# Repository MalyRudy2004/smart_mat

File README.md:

# smart_mat
Optical fiber floor mat

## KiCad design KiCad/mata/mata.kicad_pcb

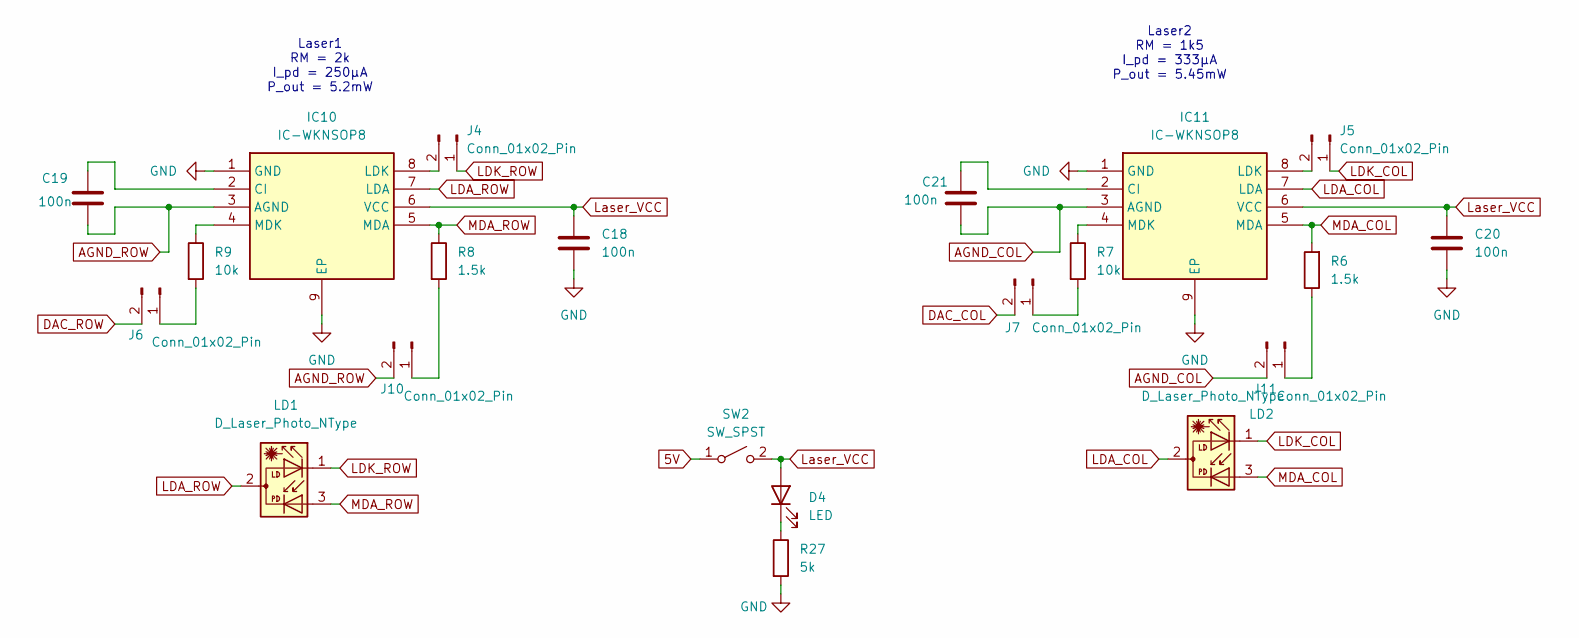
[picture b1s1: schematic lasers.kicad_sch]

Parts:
C18, C19, C20, C21: 100n; C_0805_2012Metric
D4: LED; LED_0805_2012Metric
IC10, IC11: IC-WKNSOP8; SOIC-8-1EP_3.9x4.9mm_P1.27mm_EP2.29x3mm; Manufacturer_Part_Number IC-WKNSOP8
J4, J5, J6, J7, J10, J11: Conn_01x02_Pin; PinHeader_1x02_P2.54mm_Vertical
LD1, LD2: D_Laser_Photo_NType; LaserDiode_TO56-3
R6, R8: 1.5k; R_0805_2012Metric
R7, R9: 10k; R_0805_2012Metric
R27: 5k; R_0805_2012Metric
SW2: SW_SPST; PinHeader_1x02_P2.54mm_Vertical

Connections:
5V: SW2.1 (A); also elsewhere on the board
AGND_COL: C21.2, IC11.3 (AGND), J11.2
AGND_ROW: C19.2, IC10.3 (AGND), J10.2
DAC_COL: J7.2; also elsewhere on the board
DAC_ROW: J6.2; also elsewhere on the board
GND: C18.2, C20.2, IC10.1 (GND), IC10.9 (EP), IC11.1 (GND), IC11.9 (EP), R27.2; also elsewhere on the board
LDA_COL: IC11.7 (LDA), LD2.2
LDA_ROW: IC10.7 (LDA), LD1.2
LDK_COL: J5.1, LD2.1
LDK_ROW: J4.1, LD1.1
Laser_VCC: C18.1, C20.1, D4.2 (A), IC10.6 (VCC), IC11.6 (VCC), SW2.2 (B)
MDA_COL: IC11.5 (MDA), LD2.3, R6.2
MDA_ROW: IC10.5 (MDA), LD1.3, R8.1
unnamed: D4.1 (K), R27.1
unnamed: C19.1, IC10.2 (CI)
unnamed: IC10.8 (LDK), J4.2
unnamed: IC10.4 (MDK), R9.1
unnamed: C21.1, IC11.2 (CI)
unnamed: IC11.8 (LDK), J5.2
unnamed: IC11.4 (MDK), R7.1
unnamed: J6.1, R9.2
unnamed: J7.1, R7.2
unnamed: J10.1, R8.2
unnamed: J11.1, R6.1

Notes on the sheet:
Laser2 RM = 1k5 I_pd = 333µA P_out = 5.45mW
Laser1 RM = 2k I_pd = 250µA P_out = 5.2mW

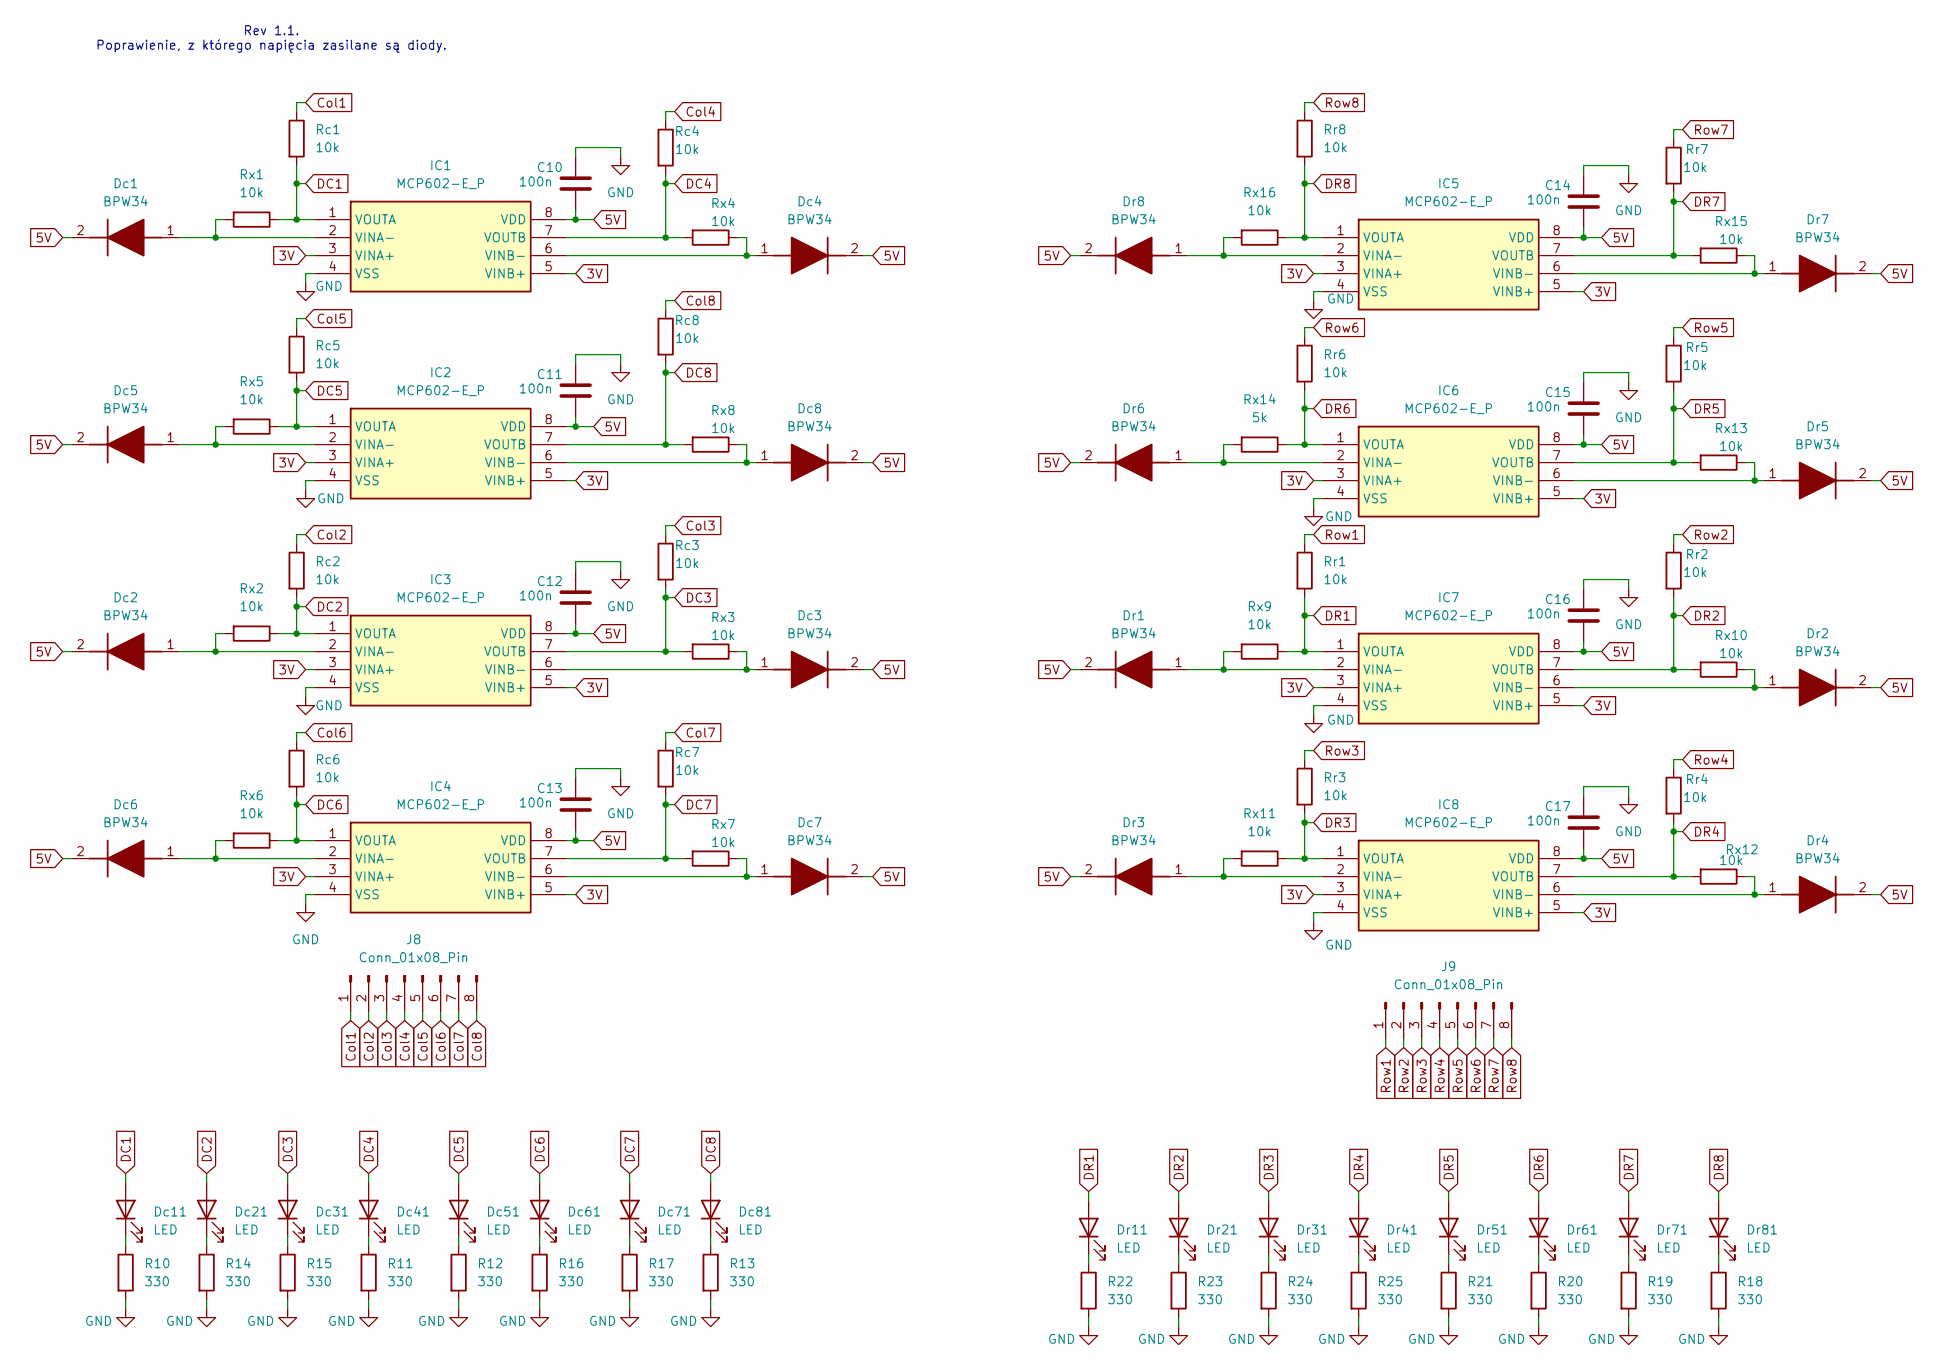
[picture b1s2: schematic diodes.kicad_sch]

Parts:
C10, C11, C12, C13, C14, C15, C16, C17: 100n; C_0805_2012Metric
Dc1, Dc2, Dc3, Dc4, Dc5, Dc6, Dc7, Dc8: BPW34; Manufacturer_Part_Number BPW34; Mouser Part Number 782-BPW34
Dc11, Dc21, Dc31, Dc41, Dc51, Dc61, Dc71, Dc81: LED; LED_0805_2012Metric
Dr1, Dr2, Dr3, Dr4, Dr5, Dr6, Dr7, Dr8: BPW34; Manufacturer_Part_Number BPW34; Mouser Part Number 782-BPW34
Dr11, Dr21, Dr31, Dr41, Dr51, Dr61, Dr71, Dr81: LED; LED_0805_2012Metric
IC1, IC2, IC3, IC4, IC5, IC6, IC7, IC8: MCP602-E_P; DIP762W56P254L930H431Q8N; Manufacturer_Part_Number MCP602-E/P; Mouser Part Number 579-MCP602-E/P
J8, J9: Conn_01x08_Pin; PinHeader_1x08_P2.54mm_Vertical
R10, R11, R12, R13, R14, R15, R16, R17, R18, R19, R20, R21, R22, R23, R24, R25: 330; R_0805_2012Metric
Rc1, Rc2, Rc3, Rc4, Rc5, Rc6, Rc7, Rc8: 10k; R_0805_2012Metric
Rr1, Rr2, Rr3, Rr4, Rr5, Rr6, Rr7, Rr8: 10k; R_0805_2012Metric
Rx1, Rx2, Rx3, Rx4, Rx5, Rx6, Rx7, Rx8, Rx9, Rx10, Rx11, Rx12, Rx13, Rx15, Rx16: 10k; R_0805_2012Metric
Rx14: 5k; R_0805_2012Metric

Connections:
3V: IC1.3 (VINA+), IC1.5 (VINB+), IC2.3 (VINA+), IC2.5 (VINB+), IC3.3 (VINA+), IC3.5 (VINB+), IC4.3 (VINA+), IC4.5 (VINB+), IC5.3 (VINA+), IC5.5 (VINB+), IC6.3 (VINA+), IC6.5 (VINB+), IC7.3 (VINA+), IC7.5 (VINB+), IC8.3 (VINA+), IC8.5 (VINB+); also elsewhere on the board
5V: C10.2, C11.2, C12.2, C13.2, C14.2, C15.2, C16.2, C17.2, Dc1.2 (K), Dc2.2 (K), Dc3.2 (K), Dc4.2 (K), Dc5.2 (K), Dc6.2 (K), Dc7.2 (K), Dc8.2 (K), Dr1.2 (K), Dr2.2 (K), Dr3.2 (K), Dr4.2 (K), Dr5.2 (K), Dr6.2 (K), Dr7.2 (K), Dr8.2 (K), IC1.8 (VDD), IC2.8 (VDD), IC3.8 (VDD), IC4.8 (VDD), IC5.8 (VDD), IC6.8 (VDD), IC7.8 (VDD), IC8.8 (VDD); also elsewhere on the board
Col1: J8.1, Rc1.1; also elsewhere on the board
Col2: J8.2, Rc2.1; also elsewhere on the board
Col3: J8.3, Rc3.1; also elsewhere on the board
Col4: J8.4, Rc4.1; also elsewhere on the board
Col5: J8.5, Rc5.1; also elsewhere on the board
Col6: J8.6, Rc6.1; also elsewhere on the board
Col7: J8.7, Rc7.1; also elsewhere on the board
Col8: J8.8, Rc8.1; also elsewhere on the board
DC1: Dc11.2 (A), IC1.1 (VOUTA), Rc1.2, Rx1.1
DC2: Dc21.2 (A), IC3.1 (VOUTA), Rc2.2, Rx2.1
DC3: Dc31.2 (A), IC3.7 (VOUTB), Rc3.2, Rx3.2
DC4: Dc41.2 (A), IC1.7 (VOUTB), Rc4.2, Rx4.2
DC5: Dc51.2 (A), IC2.1 (VOUTA), Rc5.2, Rx5.1
DC6: Dc61.2 (A), IC4.1 (VOUTA), Rc6.2, Rx6.1
DC7: Dc71.2 (A), IC4.7 (VOUTB), Rc7.2, Rx7.2
DC8: Dc81.2 (A), IC2.7 (VOUTB), Rc8.2, Rx8.2
DR1: Dr11.2 (A), IC7.1 (VOUTA), Rr1.2, Rx9.1
DR2: Dr21.2 (A), IC7.7 (VOUTB), Rr2.2, Rx10.2
DR3: Dr31.2 (A), IC8.1 (VOUTA), Rr3.2, Rx11.1
DR4: Dr41.2 (A), IC8.7 (VOUTB), Rr4.2, Rx12.2
DR5: Dr51.2 (A), IC6.7 (VOUTB), Rr5.2, Rx13.2
DR6: Dr61.2 (A), IC6.1 (VOUTA), Rr6.2, Rx14.1
DR7: Dr71.2 (A), IC5.7 (VOUTB), Rr7.2, Rx15.2
DR8: Dr81.2 (A), IC5.1 (VOUTA), Rr8.2, Rx16.1
GND: C10.1, C11.1, C12.1, C13.1, C14.1, C15.1, C16.1, C17.1, IC1.4 (VSS), IC2.4 (VSS), IC3.4 (VSS), IC4.4 (VSS), IC5.4 (VSS), IC6.4 (VSS), IC7.4 (VSS), IC8.4 (VSS), R10.2, R11.2, R12.2, R13.2, R14.2, R15.2, R16.2, R17.2, R18.2, R19.2, R20.2, R21.2, R22.2, R23.2, R24.2, R25.2; also elsewhere on the board
unnamed: Dc1.1 (A), IC1.2 (VINA-), Rx1.2
unnamed: Dc2.1 (A), IC3.2 (VINA-), Rx2.2
unnamed: Dc3.1 (A), IC3.6 (VINB-), Rx3.1
unnamed: Dc4.1 (A), IC1.6 (VINB-), Rx4.1
unnamed: Dc5.1 (A), IC2.2 (VINA-), Rx5.2
unnamed: Dc6.1 (A), IC4.2 (VINA-), Rx6.2
unnamed: Dc7.1 (A), IC4.6 (VINB-), Rx7.1
unnamed: Dc8.1 (A), IC2.6 (VINB-), Rx8.1
unnamed: Dc11.1 (K), R10.1
unnamed: Dc21.1 (K), R14.1
unnamed: Dc31.1 (K), R15.1
unnamed: Dc41.1 (K), R11.1
unnamed: Dc51.1 (K), R12.1
unnamed: Dc61.1 (K), R16.1
unnamed: Dc71.1 (K), R17.1
unnamed: Dc81.1 (K), R13.1
unnamed: Dr1.1 (A), IC7.2 (VINA-), Rx9.2
unnamed: Dr2.1 (A), IC7.6 (VINB-), Rx10.1
unnamed: Dr3.1 (A), IC8.2 (VINA-), Rx11.2
unnamed: Dr4.1 (A), IC8.6 (VINB-), Rx12.1
unnamed: Dr5.1 (A), IC6.6 (VINB-), Rx13.1
unnamed: Dr6.1 (A), IC6.2 (VINA-), Rx14.2
unnamed: Dr7.1 (A), IC5.6 (VINB-), Rx15.1
unnamed: Dr8.1 (A), IC5.2 (VINA-), Rx16.2
unnamed: Dr11.1 (K), R22.1
unnamed: Dr21.1 (K), R23.1
unnamed: Dr31.1 (K), R24.1
unnamed: Dr41.1 (K), R25.1
unnamed: Dr51.1 (K), R21.1
unnamed: Dr61.1 (K), R20.1
unnamed: Dr71.1 (K), R19.1
unnamed: Dr81.1 (K), R18.1
Row1: J9.1, Rr1.1; also elsewhere on the board
Row2: J9.2, Rr2.1; also elsewhere on the board
Row3: J9.3, Rr3.1; also elsewhere on the board
Row4: J9.4, Rr4.1; also elsewhere on the board
Row5: J9.5, Rr5.1; also elsewhere on the board
Row6: J9.6, Rr6.1; also elsewhere on the board
Row7: J9.7, Rr7.1; also elsewhere on the board
Row8: J9.8, Rr8.1; also elsewhere on the board

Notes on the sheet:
Rev 1.1. Poprawienie, z którego napięcia zasilane są diody.

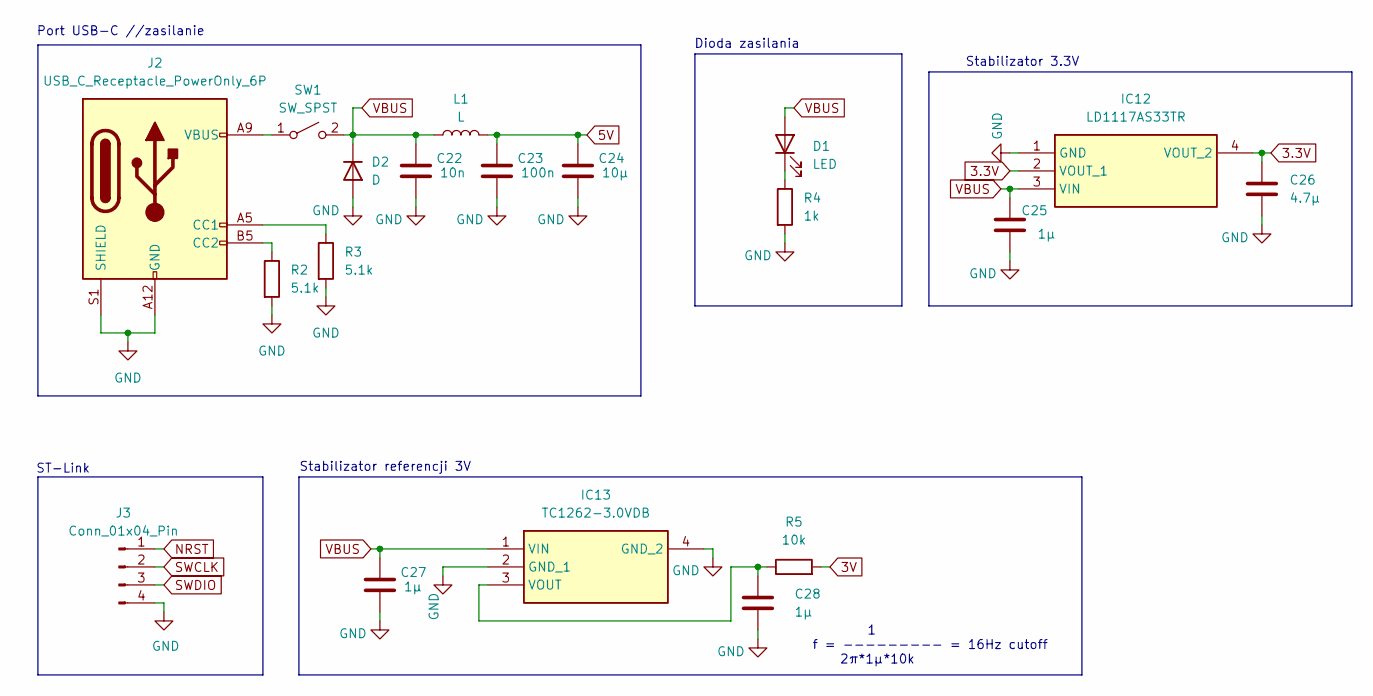
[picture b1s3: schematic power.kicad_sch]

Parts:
C22: 10n; C_0805_2012Metric
C23: 100n; C_0805_2012Metric
C24: 10µ; C_0805_2012Metric
C25, C27, C28: 1µ; C_0805_2012Metric
C26: 4.7µ; C_0805_2012Metric
D1: LED; LED_0805_2012Metric
D2: D; SM2T6V8A
IC12: LD1117AS33TR; SOT230P700X180-4N; Manufacturer_Part_Number LDL1117S33R; Mouser Part Number 511-LDL1117S33R
IC13: TC1262-3.0VDB; SOT230P700X180-4N; Manufacturer_Part_Number TC1262-3.0VDB; Mouser Part Number 579-TC1262-3.0VDB
J2: USB_C_Receptacle_PowerOnly_6P; USB_C_Receptacle_GCT_USB4125-xx-x-0190_6P_TopMnt_Horizontal
J3: Conn_01x04_Pin; PinHeader_1x04_P2.54mm_Vertical
L1: L; L_1806_4516Metric
R2, R3: 5.1k; R_0805_2012Metric
R4: 1k; R_0805_2012Metric
R5: 10k; R_0805_2012Metric
SW1: SW_SPST; PinHeader_1x02_P2.54mm_Vertical

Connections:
3.3V: C26.1, IC12.2 (VOUT_1), IC12.4 (VOUT_2); also elsewhere on the board
3V: R5.2; also elsewhere on the board
5V: C23.1, C24.1, L1.2; also elsewhere on the board
GND: C22.2, C23.2, C24.2, C25.2, C26.2, C27.2, C28.2, D2.2 (A), IC12.1 (GND), IC13.2 (GND_1), IC13.4 (GND_2), J2.A12 (GND), J2.B12 (GND), J2.S1 (SHIELD), J3.4, R2.2, R3.2, R4.2; also elsewhere on the board
NRST: J3.1; also elsewhere on the board
unnamed: D1.1 (K), R4.1
unnamed: C28.1, IC13.3 (VOUT), R5.1
unnamed: J2.A5 (CC1), R3.1
unnamed: J2.B5 (CC2), R2.1
unnamed: J2.A9 (VBUS), J2.B9 (VBUS), SW1.1 (A)
SWCLK: J3.2; also elsewhere on the board
SWDIO: J3.3; also elsewhere on the board
VBUS: C22.1, C25.1, C27.1, D1.2 (A), D2.1 (K), IC12.3 (VIN), IC13.1 (VIN), L1.1, SW1.2 (B)

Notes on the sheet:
ST-Link
Dioda zasilania
Port USB-C //zasilanie
1 f = --------- = 16Hz cutoff 2π*1µ*10k
Stabilizator referencji 3V
Stabilizator 3.3V

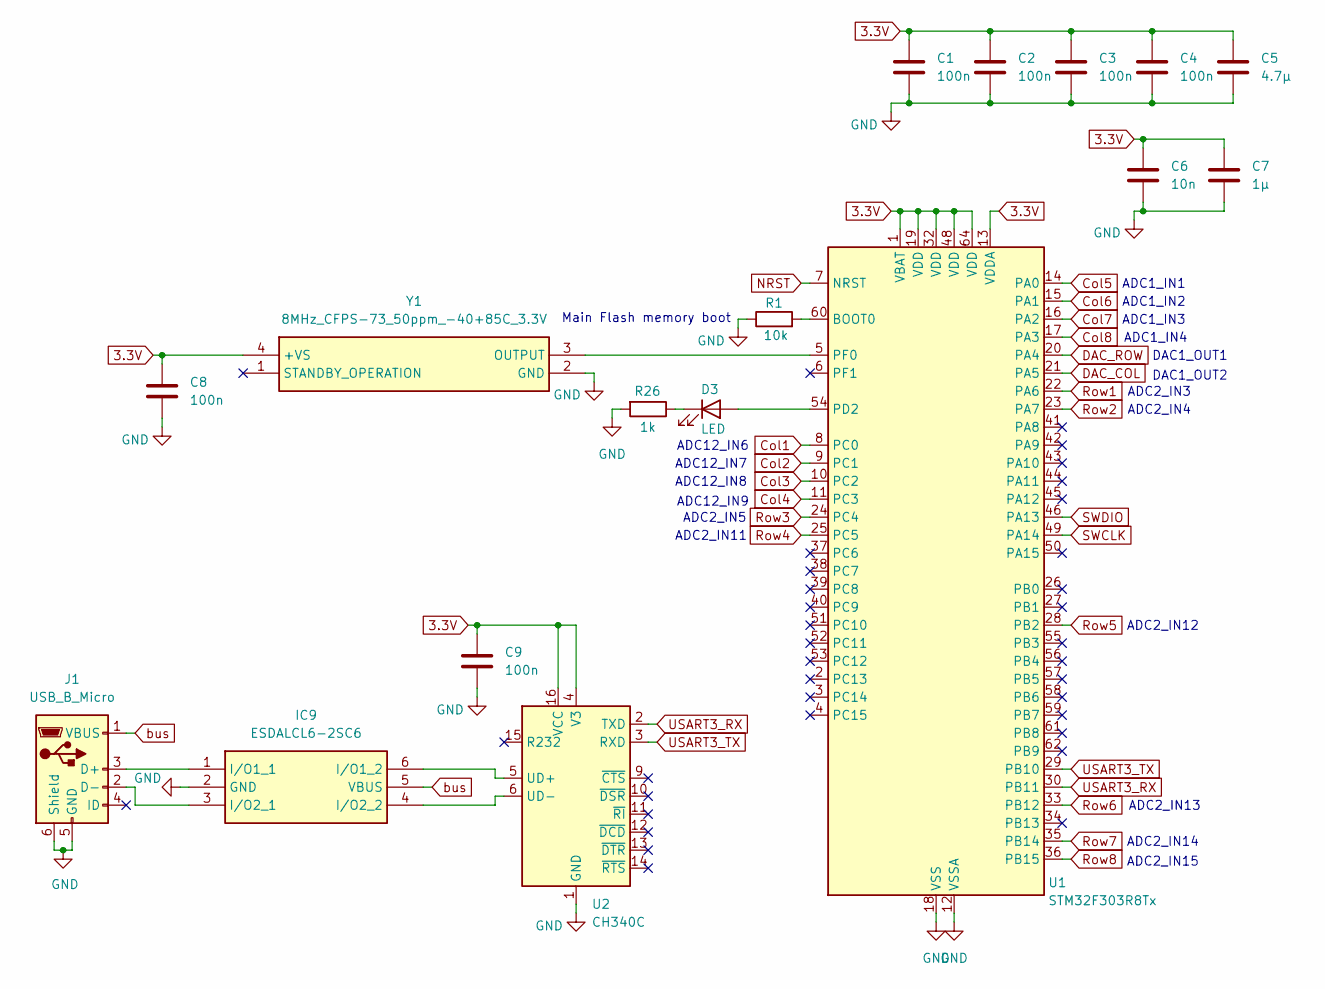
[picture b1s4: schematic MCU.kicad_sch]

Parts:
C1, C2, C3, C4, C8, C9: 100n; C_0805_2012Metric
C5: 4.7µ; C_0805_2012Metric
C6: 10n; C_0805_2012Metric
C7: 1µ; C_0805_2012Metric
D3: LED; LED_0805_2012Metric
IC9: ESDALCL6-2SC6; SOT95P280X145-6N; Manufacturer_Part_Number ESDALCL6-2SC6; Mouser Part Number 511-ESDALCL6-2SC6
J1: USB_B_Micro; USB_Micro-B_GCT_USB3076-30-A
R1: 10k; R_0805_2012Metric
R26: 1k; R_0805_2012Metric
U1: STM32F303R8Tx; LQFP-64_10x10mm_P0.5mm
U2: CH340C; SOIC-16_3.9x9.9mm_P1.27mm
Y1: 8MHz_CFPS-73_50ppm_-40+85C_3.3V; CFPS-73_1; Manufacturer_Part_Number 25.0MHz CFPS-73 ±50ppm -40+85°C 3.3V

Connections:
3.3V: C1.1, C2.1, C3.1, C4.1, C5.1, C6.1, C7.1, C8.1, C9.1, U1.1 (VBAT), U1.13 (VDDA), U1.19 (VDD), U1.32 (VDD), U1.48 (VDD), U1.64 (VDD), U2.4 (V3), U2.16 (VCC), Y1.4 (+VS); also elsewhere on the board
Col1: U1.8 (PC0); also elsewhere on the board
Col2: U1.9 (PC1); also elsewhere on the board
Col3: U1.10 (PC2); also elsewhere on the board
Col4: U1.11 (PC3); also elsewhere on the board
Col5: U1.14 (PA0); also elsewhere on the board
Col6: U1.15 (PA1); also elsewhere on the board
Col7: U1.16 (PA2); also elsewhere on the board
Col8: U1.17 (PA3); also elsewhere on the board
DAC_COL: U1.21 (PA5); also elsewhere on the board
DAC_ROW: U1.20 (PA4); also elsewhere on the board
GND: C1.2, C2.2, C3.2, C4.2, C5.2, C6.2, C7.2, C8.2, C9.2, IC9.2 (GND), J1.5 (GND), J1.6 (Shield), R1.1, R26.2, U1.12 (VSSA), U1.18 (VSS), U1.31 (VSS), U1.47 (VSS), U1.63 (VSS), U2.1 (GND), Y1.2 (GND); also elsewhere on the board
NRST: U1.7 (NRST); also elsewhere on the board
unnamed: D3.2 (A), U1.54 (PD2)
unnamed: D3.1 (K), R26.1
unnamed: IC9.1 (I/O1_1), J1.3 (D+)
unnamed: IC9.6 (I/O1_2), U2.5 (UD+)
unnamed: IC9.3 (I/O2_1), J1.2 (D-)
unnamed: IC9.4 (I/O2_2), U2.6 (UD-)
unnamed: R1.2, U1.60 (BOOT0)
unnamed: U1.5 (PF0), Y1.3 (OUTPUT)
Row1: U1.22 (PA6); also elsewhere on the board
Row2: U1.23 (PA7); also elsewhere on the board
Row3: U1.24 (PC4); also elsewhere on the board
Row4: U1.25 (PC5); also elsewhere on the board
Row5: U1.28 (PB2); also elsewhere on the board
Row6: U1.33 (PB12); also elsewhere on the board
Row7: U1.35 (PB14); also elsewhere on the board
Row8: U1.36 (PB15); also elsewhere on the board
SWCLK: U1.49 (PA14); also elsewhere on the board
SWDIO: U1.46 (PA13); also elsewhere on the board
USART3_RX: U1.30 (PB11), U2.2 (TXD)
USART3_TX: U1.29 (PB10), U2.3 (RXD)
bus: IC9.5 (VBUS), J1.1 (VBUS)

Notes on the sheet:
Main Flash memory boot
ADC2_IN14
ADC12_IN8
ADC12_IN7
ADC2_IN11
DAC1_OUT2
ADC1_IN4
ADC2_IN3
ADC1_IN3
ADC2_IN12
ADC12_IN6
ADC2_IN5
ADC1_IN2
ADC2_IN13
DAC1_OUT1
ADC1_IN1
ADC2_IN15
ADC2_IN4
ADC12_IN9

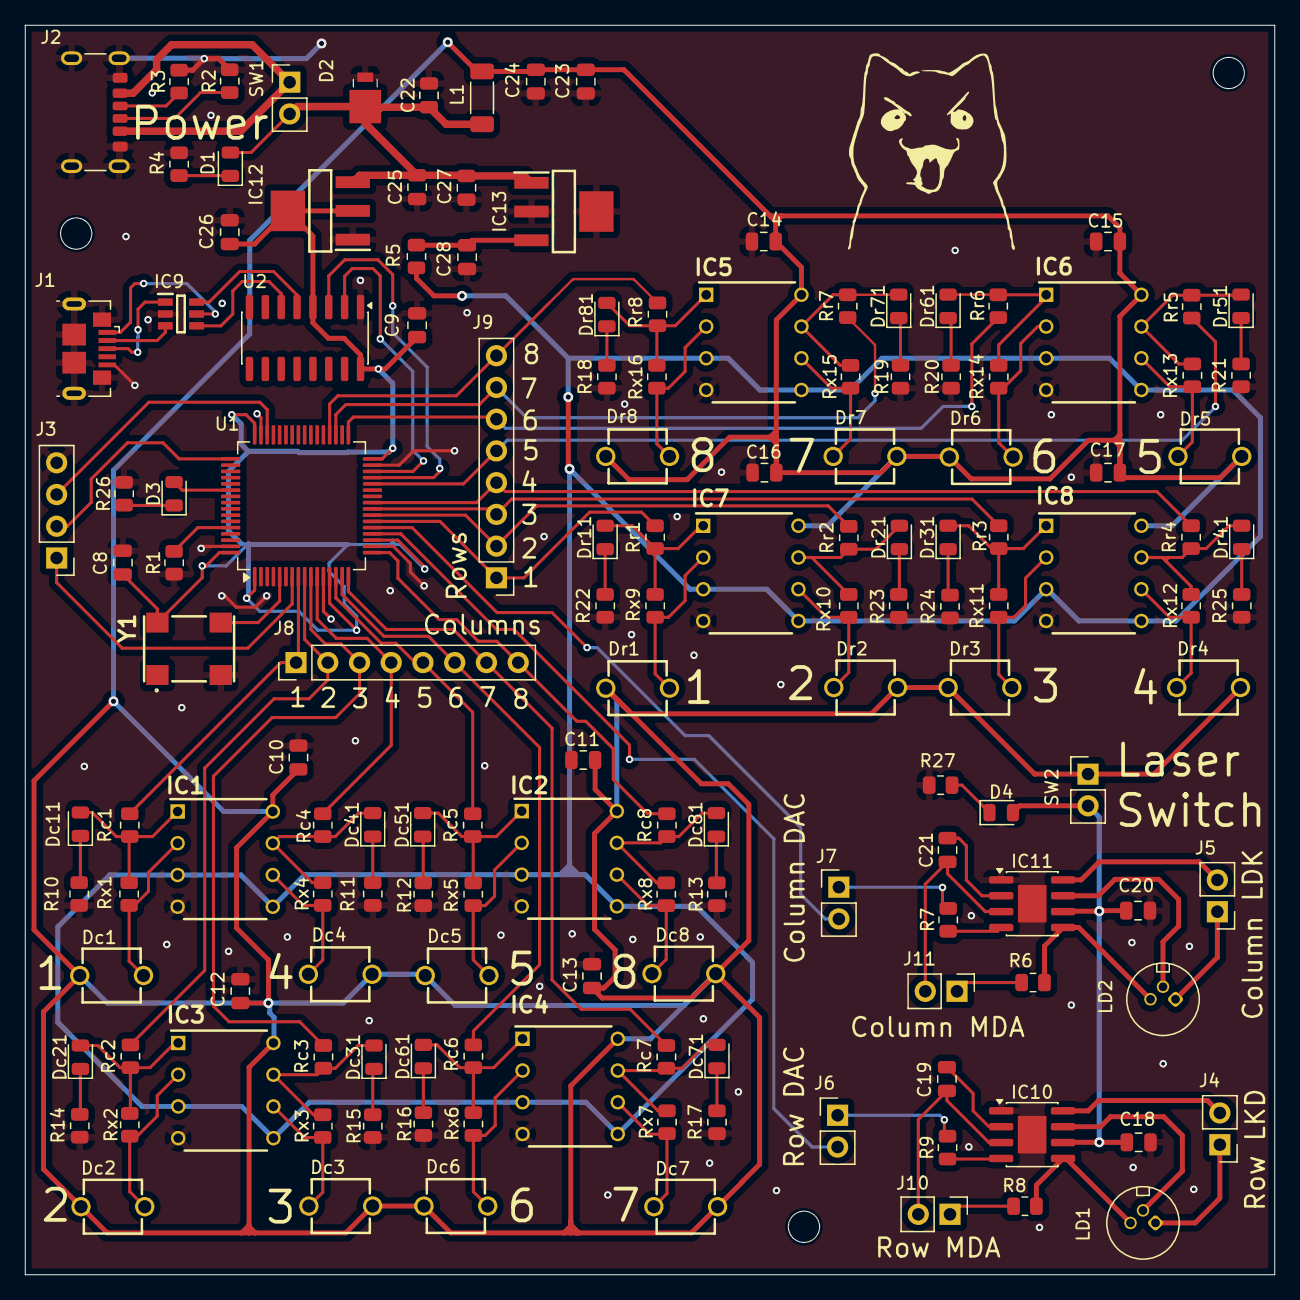
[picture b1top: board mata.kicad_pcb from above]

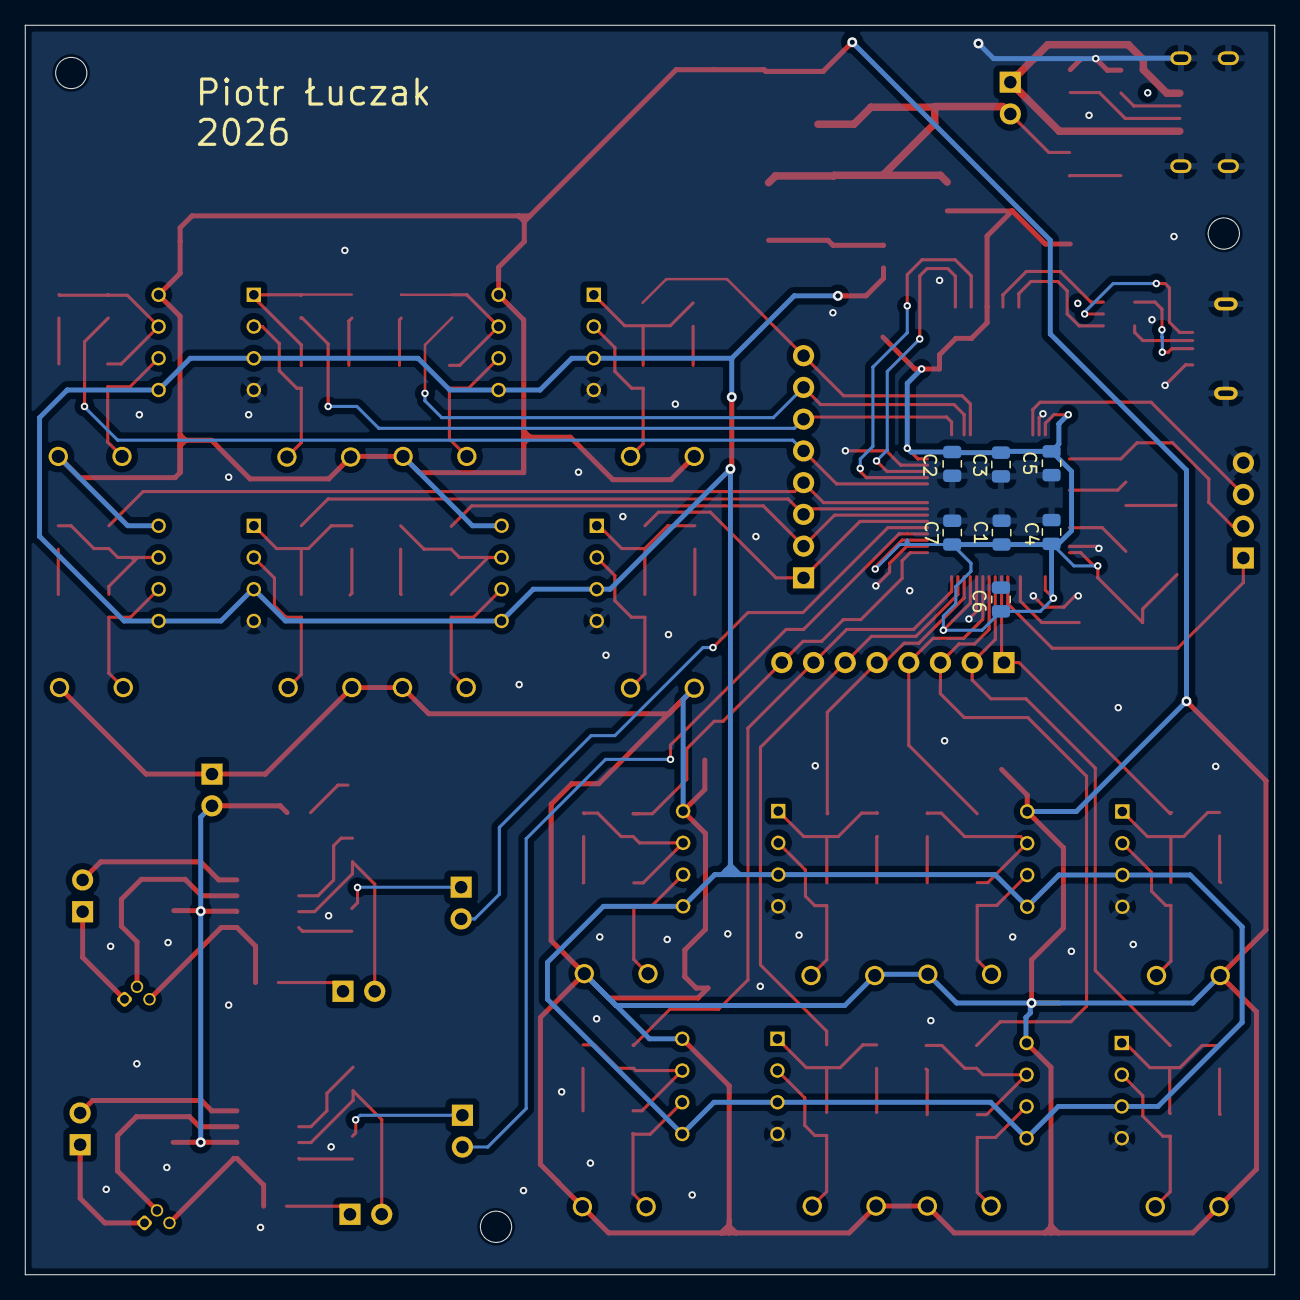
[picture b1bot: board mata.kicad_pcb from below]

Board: 2 copper layers, 100.0 x 100.0 mm, 155 parts (7 on the bottom side), 110 nets.
